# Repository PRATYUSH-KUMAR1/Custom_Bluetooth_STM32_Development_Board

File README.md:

# Custom_Bluetooth_STM32_Development_Board

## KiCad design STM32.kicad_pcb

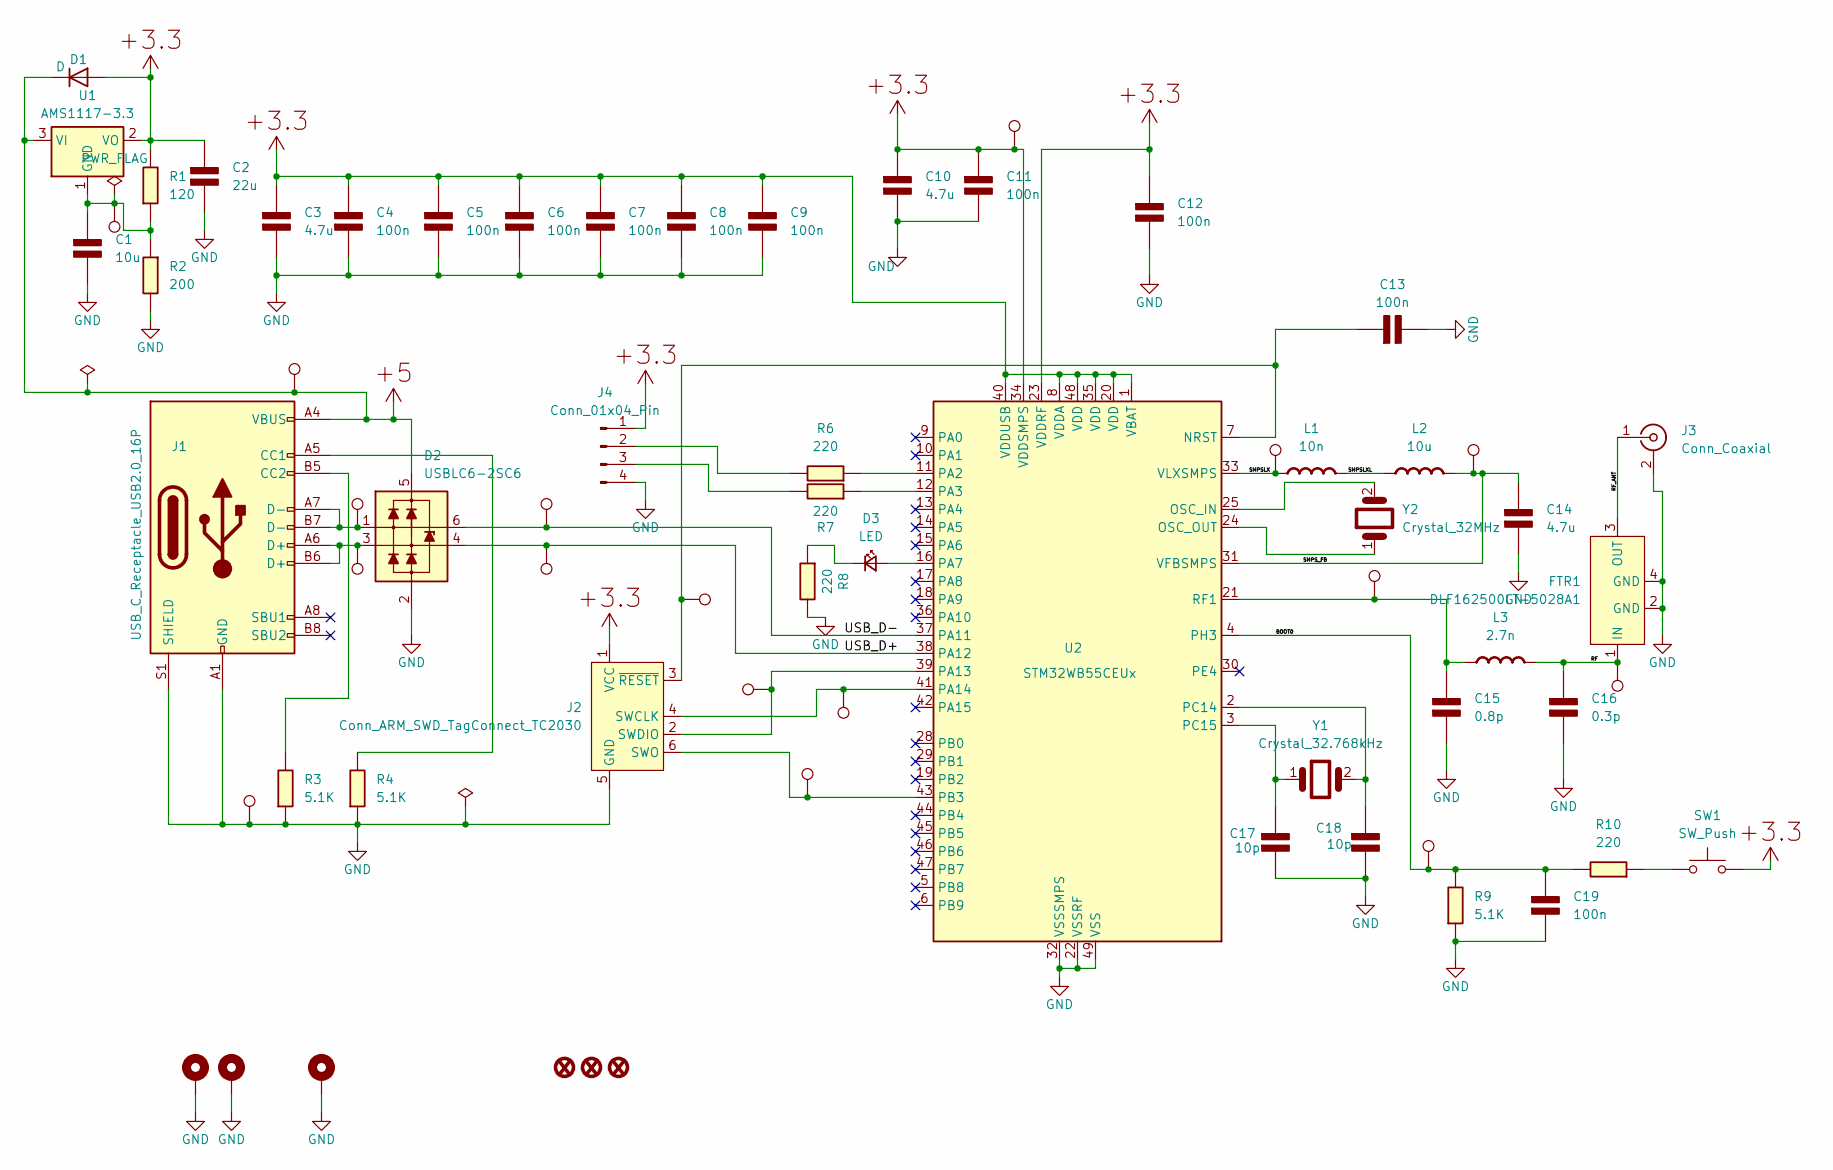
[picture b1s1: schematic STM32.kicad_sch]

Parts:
C1: 10u; C_0402_1005Metric; Rating V
C2: 22u; C_0402_1005Metric; Rating V
C3, C10, C14: 4.7u; C_0603_1608Metric; Rating V
C4, C5, C6, C7, C8, C9, C11, C12, C13, C19: 100n; C_0402_1005Metric; Rating V
C15: 0.8p; C_0402_1005Metric; Rating V
C16: 0.3p; C_0402_1005Metric; Rating V
C17, C18: 10p; C_0402_1005Metric; Rating V
D1: D; D_0805_2012Metric
D2: USBLC6-2SC6; SOT-23-6
D3: LED; LED_0603_1608Metric
FID1, FID2, FID3: Fiducial_0.5mm; Fiducial_0.5mm_Mask1mm
FTR1: DLF162500LT-5028A1
H1, H2, H4: MountingHole_Pad; MountingHole_2.2mm_M2_DIN965_Pad
J1: USB_C_Receptacle_USB2.0_16P; USB_C_Receptacle_GCT_USB4105-xx-A_16P_TopMnt_Horizontal
J2: Conn_ARM_SWD_TagConnect_TC2030; Tag-Connect_TC2030-IDC-FP_2x03_P1.27mm_Vertical
J3: Conn_Coaxial; U.FL_Hirose_U.FL-R-SMT-1_Vertical
J4: Conn_01x04_Pin; Molex_PicoBlade_53048-0410_1x04_P1.25mm_Horizontal
L1: 10n; L_0402_1005Metric; Rating A
L2: 10u; L_0805_2012Metric; Rating A
L3: 2.7n; L_0402_1005Metric; Rating A
R1: 120; R_1206
R2: 200; R_1206
R3, R4, R9: 5.1K; R_1206
R6, R7, R8, R10: 220; R_1206
SW1: SW_Push; SW_SPST_B3S-1000
TP1, TP2, TP3, TP4, TP6, TP7, TP8, TP9, TP10, TP13, TP14, TP15, TP16, TP17, TP19, TP21, TP22: TestPoint; TestPoint_Pad_D1.0mm
U1: AMS1117-3.3; SOT-223-3_TabPin2
U2: STM32WB55CEUx; QFN-48-1EP_7x7mm_P0.5mm_EP5.6x5.6mm
Y1: Crystal_32.768kHz; Crystal_AT310_D3.0mm_L10.0mm_Horizontal
Y2: Crystal_32MHz; Crystal_HC49-4H_Vertical

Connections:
/BOOT0: C19.1 (+), R9.1, R10.1, TP13.1, U2.4 (PH3)
/RF: C16.1 (+), FTR1.1 (IN), L3.2 (-), TP9.1
/RF_ANT: FTR1.3 (OUT), J3.1 (In)
/SMPSLX: L1.1 (+), TP22.1, U2.33 (VLXSMPS)
/SMPSLXL: L1.2 (-), L2.1 (+)
/SMPS_FB: C14.1 (+), L2.2 (-), TP10.1, U2.31 (VFBSMPS)
/USB_D+: D2.4 (L2), TP15.1, U2.38 (PA12)
/USB_D-: D2.6 (L1), TP14.1, U2.37 (PA11)
GND: C1.2 (-), C2.2 (-), C3.2 (-), C4.2 (-), C5.2 (-), C6.2 (-), C7.2 (-), C8.2 (-), C9.2 (-), C10.2 (-), C11.2 (-), C12.2 (-), C13.2 (-), C14.2 (-), C15.2 (-), C16.2 (-), C17.2 (-), C18.2 (-), C19.2 (-), D2.2 (VN), FTR1.2 (GND), FTR1.4 (GND), H1.1, H2.1, H4.1, J1.A1 (GND), J1.A12 (GND), J1.B1 (GND), J1.B12 (GND), J1.S1 (SHIELD), J2.5 (GND), J3.2 (Ext), J4.4, R2.1, R3.2, R4.2, R8.1, R9.2, TP7.1, U2.22 (VSSRF), U2.32 (VSSSMPS), U2.49 (VSS)
unnamed: C1.1 (+), R1.2, R2.2, TP21.1, U1.1 (GND)
unnamed: C13.1 (+), J2.3 (~RESET), TP4.1, U2.7 (NRST)
unnamed: C15.1 (+), L3.1 (+), TP8.1, U2.21 (RF1)
unnamed: C17.1 (+), U2.3 (PC15), Y1.1
unnamed: C18.1 (+), U2.2 (PC14), Y1.2
unnamed: D2.1 (L1), J1.A7 (D-), J1.B7 (D-), TP16.1
unnamed: D2.3 (L2), J1.A6 (D+), J1.B6 (D+), TP17.1
unnamed: D3.2 (A), U2.16 (PA7)
unnamed: D3.1 (K), R8.2
unnamed: J1.A5 (CC1), R4.1
unnamed: J1.B5 (CC2), R3.1
unnamed: J2.4 (SWCLK), TP2.1, U2.41 (PA14)
unnamed: J2.2 (SWDIO), TP3.1, U2.39 (PA13)
unnamed: J2.6 (SWO), TP1.1, U2.43 (PB3)
unnamed: J4.2, R6.1
unnamed: J4.3, R7.1
unnamed: R10.2, SW1.1
unnamed: U2.25 (OSC_IN), Y2.2
unnamed: U2.24 (OSC_OUT), Y2.1
unnamed: R6.2, U2.11 (PA2)
unnamed: R7.2, U2.12 (PA3)
P,+3.3: C2.1 (+), C3.1 (+), C4.1 (+), C5.1 (+), C6.1 (+), C7.1 (+), C8.1 (+), C9.1 (+), C10.1 (+), C11.1 (+), C12.1 (+), D1.2 (A), J2.1 (VCC), J4.1, R1.1, SW1.2, TP19.1, U1.2 (VO), U2.1 (VBAT), U2.8 (VDDA), U2.20 (VDD), U2.23 (VDDRF), U2.34 (VDDSMPS), U2.35 (VDD), U2.40 (VDDUSB), U2.48 (VDD)
P,+5: D1.1 (K), D2.5 (VP), J1.A4 (VBUS), J1.A9 (VBUS), J1.B4 (VBUS), J1.B9 (VBUS), TP6.1, U1.3 (VI)

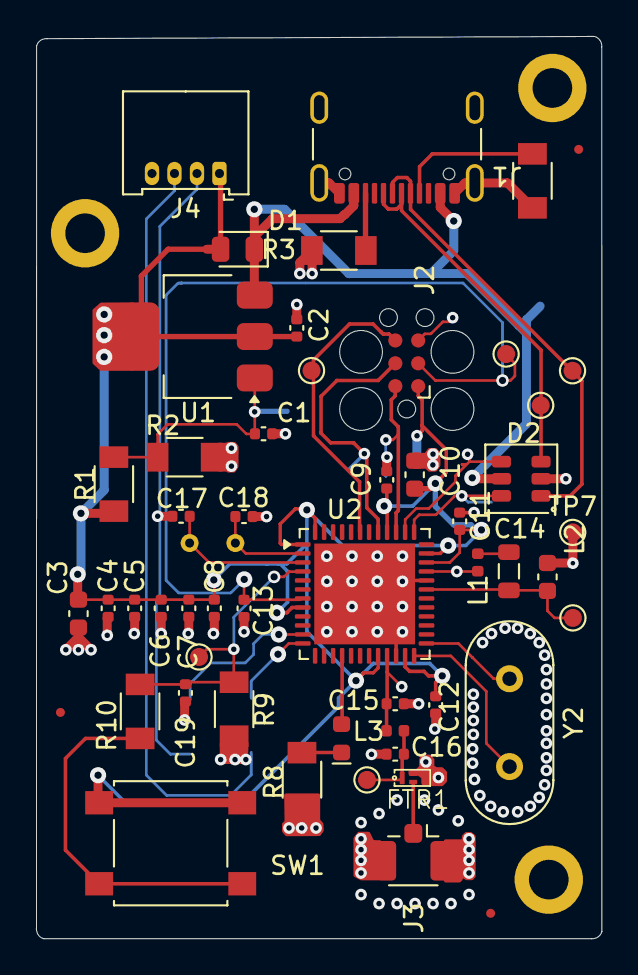
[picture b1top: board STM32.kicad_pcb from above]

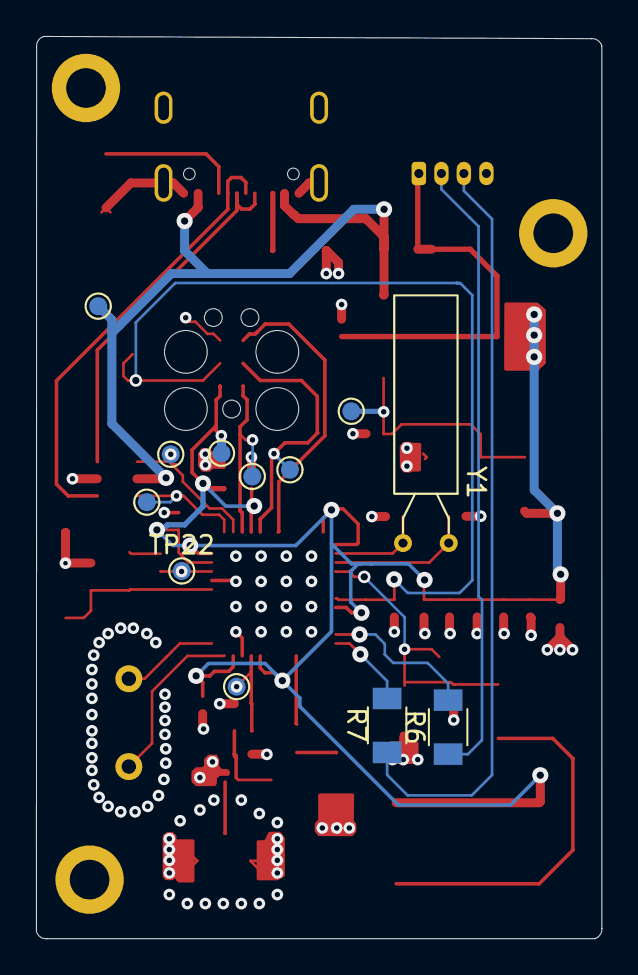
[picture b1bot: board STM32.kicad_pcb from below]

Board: 4 copper layers, 31.4 x 50.1 mm, 67 parts (12 on the bottom side), 32 nets.

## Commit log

2026-04-18 added the scametic,footprint/pcb layout left- 18/04/2026-11:12 AM
2026-04-23 design-compleat; verificaton,revision-remaning
2026-04-24 adding zip as an backup
2026-04-24 revision-1
2026-04-24 added test points
2026-04-24 revision-2
2026-04-28 revision-3 done gurber file nedded
